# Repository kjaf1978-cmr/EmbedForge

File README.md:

# EmbedForge

An offline-first desktop application that turns a plain-English description and a target
board into a verified, documented Arduino / Raspberry Pi / Pico project: firmware, pin map,
schematic, breadboard, PCB or perfboard, manufacturing files, BOM, emulation and assembly
guide.

Licence: GPL-3.0-or-later (LICENSE file added with the first code, Increment 1).

## Current state
**Increment 1 in progress.** Phase 0 is approved with conditions (docs/phase0/phase0_gate_report.md).
WP 1.1 (Rust core), WP 1.2 (application shell and UI) and WP 1.3 (packaging, signing,
installers, privileged-helper skeleton) are done; reports in docs/inc1/.

- Requirements baseline: `docs/requirements/EmbedForge_prompt_v3.8.md`
- v3 review findings (D9): `docs/requirements/v3_review_findings.md`
- Phase 0 tracker and decisions: `docs/phase0/STATUS.md`
- Session log: `docs/SESSION_LOG.md`

## Layout
```
docs/requirements/   build prompt baselines, review findings, change logs
docs/phase0/         Phase 0 deliverables (a)–(o)
docs/inc1/           Increment 1 scope and reports
core/                Rust workspace: ef-schema, ef-cm, ef-integrity, ef-host, ef-diag,
                     ef-pack (packs, media, bootstrap), ef-helper (SS-05 policy), ef-release
app/ui/              UI (Preact + TypeScript + Vite), unit and browser tests
app/src-tauri/       Tauri 2 desktop shell
packaging/           staging tree, .deb and Windows (NSIS) installers, test media
docs/release/        signing and key-rotation procedure (SEC-02)
spikes/              Phase 0 evaluation code (not application code)
.github/workflows/   CI
tools/               scripts used to produce or check documents
```

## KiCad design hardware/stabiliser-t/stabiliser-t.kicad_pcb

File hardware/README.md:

# Boards of the worked designs (decisions D43, D44)

Each design's board as a KiCad 7 project, with its fabrication files. The boards are generated
from the app's schematics by `tools/kicad` and then checked with KiCad's design rule check
(DRC); do not edit the board files by hand without updating the plan in
`tools/kicad/layouts.ts`, or the next export overwrites the change.

| Design | Folder | Board | DRC (errors / unconnected) | Status |
|---|---|---|---|---|
| Mains voltage stabiliser 1 kVA (P4) | `stabiliser/` | 230 × 246 mm, 2 layers, 2 oz | 0 / 0 | re-routed after the review (input relay, protection relay, IRM-15 supply); the DRC report's warnings: footprint library not registered for the check (193), silkscreen overlaps (78), 4 coil stubs the router bypassed (a dangling end, no open connection); the relay footprint is provisional until checked against the 832A drawing |
| Mains change-over 1P, 32 A (P3): control board + DIN-rail panel | `changeover-1p/` | 165 × 110 mm, 2 layers, 2 oz | 0 / 0 | routed (revision B, D64: the varistors' room for the TMOV14's datasheet body); panel wiring in `panel.csv` |
| Mains change-over 3P+N, 32 A (P3): control board + DIN-rail panel | `changeover-3p/` | 235 × 155 mm, 2 layers, 2 oz | 0 / 0 | routed (revision B, D64: the varistors' room for the TMOV14's datasheet body); panel wiring in `panel.csv` |
| MPPT solar charger 48 V, 80 A (P6): power board | `mppt-power/` | 280 × 160 mm, 2 layers, 4 oz | 0 / 0 | routed; copper bars and lugs below |
| MPPT solar charger 48 V, 80 A (P6): control board | `mppt-control/` | 160 × 110 mm, 2 layers, 2 oz | 0 / 0 | routed; `link.csv`: the nets to the power board |
| Inverter 48 V 5 kW, 50 Hz transformer (P7a): power board | `inverter-lf-48-power/` | 280 × 170 mm, 2 layers, 4 oz | 0 / 0 | routed; copper bars and lugs, bus and ground planes |
| Inverter 48 V 5 kW, 50 Hz transformer (P7a): control board | `inverter-lf-48-control/` | 200 × 150 mm, 2 layers, 2 oz | 0 / 0 | routed; mains nets 3.2 mm apart |
| Inverter 48 V 5 kW, high-frequency (P7b): battery-side power board | `inverter-hf-48-power-lv/` | 180 × 230 mm, 2 layers, 4 oz | 0 / 0 | routed; copper bars, the current transformer off-board |
| Inverter 48 V 5 kW, high-frequency (P7b): 380 V power board | `inverter-hf-48-power-hv/` | 140 × 270 mm, 2 layers, 4 oz | 0 / 0 | routed; conformal coating required (0.8 mm, IPC-2221 B4); the drivers' HVG poured after routing |
| Inverter 48 V 5 kW, high-frequency (P7b): battery-side control board | `inverter-hf-48-control-lv/` | 220 × 160 mm, 2 layers, 2 oz | 0 / 0 | routed; `panel.csv`: the nets to the other boards (J_PANEL, J_PANEL2) |
| Inverter 48 V 5 kW, high-frequency (P7b): 380 V control board | `inverter-hf-48-control-hv/` | 340 × 240 mm, 2 layers, 2 oz | 0 / 0 | routed; 380 V nets 2.5 mm from the battery side; HVG poured on both layers; 77 links drawn by `tools/kicad/autolink.py`; `panel.csv`: the nets to the other boards |
| Inverter 12 V 1.5 kW, 50 Hz transformer (P7a): power board | `inverter-lf-12-power/` | 280 × 170 mm, 2 layers, 4 oz | 0 / 0 | routed; the 48 V board's plan with six 4700 µF bus capacitors |
| Inverter 12 V 1.5 kW, 50 Hz transformer (P7a): control board | `inverter-lf-12-control/` | 200 × 150 mm, 2 layers, 2 oz | 0 / 0 | routed; mains nets 3.2 mm apart; one link drawn by `tools/kicad/link.py` |
| Inverter 12 V 1.5 kW, high-frequency (P7b): battery-side power board | `inverter-hf-12-power-lv/` | 260 × 230 mm, 2 layers, 4 oz | 0 / 0 | routed; three MOSFETs per switch (twelve in the row), copper bars |
| Inverter 12 V 1.5 kW, high-frequency (P7b): 380 V power board | `inverter-hf-12-power-hv/` | 140 × 270 mm, 2 layers, 4 oz | 0 / 0 | routed; the 48 V board's plan; conformal coating required |
| Inverter 12 V 1.5 kW, high-frequency (P7b): battery-side control board | `inverter-hf-12-control-lv/` | 220 × 160 mm, 2 layers, 2 oz | 0 / 0 | routed; `panel.csv`: the nets to the other boards |
| Inverter 12 V 1.5 kW, high-frequency (P7b): 380 V control board | `inverter-hf-12-control-hv/` | 340 × 240 mm, 2 layers, 2 oz | 0 / 0 | routed; as the 48 V one (HVG pours, links by `autolink.py`) |
| Gate controller 24 V (P9, D25): motor drive, protections, Arduino Nano and IR receiver | `gate-controller/` | 160 × 110 mm, 2 layers, 2 oz | 0 / 0 | routed (revision D, after the independent review: a power-on reset, CLR by its edge, a trip drops the relays, a 0.1 s blanking, STOP, the photo-beam transmitter switched for its test, a key-switch input, a CUT-OFF LED; revision C: the close limit and the photo-beam on separate inputs, a LEARN button, the relays on the 832A footprint) |
| Pump controller (P9): tank level, dry source, timers | `pump-control/` | 165 × 110 mm, 2 layers, 2 oz | 0 / 0 | routed (revision C, P9 audit and review): the control is SELV (not earthed), the only mains on the board the safety transformer's fused primary, 5.5 mm from the control; the relays (reinforced interface relays), contactor and breaker on the DIN rail per `panel.csv` |
| Cordless trimmer drive 36 V (P9) | `trimmer-drive/` | 160 × 100 mm, 2 layers, 4 oz | 0 / 0 | routed; power on 3 mm tracks, ground poured on both layers |
| Block moulding machine (P9): safety circuit, high-side outputs, inputs and Arduino Mega 2560 + DIN-rail panel | `block-machine/` | 260 × 180 mm, 2 layers, 2 oz | 0 / 0 | routed (revision C after the second review: the 24 V supplies on their own block, the enable MOSFET on TO-220, F3, K5 for the feeder and vibrators; revision B, D65 … D67: the safety relays, the safety and motor contactors, the breakers on the DIN rail; the outputs switched on their +24 V side with the common enable and read-back; the Mega 2560 under the board, its jacks at the right edge); wiring in `panel.csv`; no 400 V net on the board |
| Irrigation controller (P9, D24): main board | `irrigation-main/` | 130 × 100 mm, 2 layers, 2 oz | 0 / 0 | routed; ESP32-DevKitC on sockets (antenna over the top edge), 24 V in, bus to the modules (20-way ribbon) |
| Irrigation controller (P9, D24): 8-zone channel module (1 … 8 per controller) | `irrigation-module/` | 230 × 95 mm, 2 layers, 2 oz | 0 / 0 | routed; field terminals along the bottom edge (per zone: valve +24 V, valve out, sensor +3.3 V, signal, 0 V); bus in top left, out top right |
| Grinder drive 2.5 kW, 240 V (P9, D26/D46): power board | `grinder-240-power/` | 160 × 110 mm, 2 layers, 4 oz | 0 / 0 | routed; GBPC3510 bridge and both IKW50N60T on the bottom edge (one heatsink, insulating pads), 3 mm power tracks, ground poured on both layers; the whole board at mains potential: 0.8 mm between nets (1.5 mm around the mains input), conformal coating required; the 15 mH choke, the motor and the contactor KM on the panel (`panel.csv`) |
| Grinder drive 2.5 kW, 240 V (P9, D26/D46): control board | `grinder-240-control/` | 180 × 130 mm, 2 layers, 2 oz | 0 / 0 | routed (the run chain and the speed pot moved to the operator interface board); the five trimmers (MAX, MIN, ACCEL, CURRENT LIMIT, IR COMP), terminals for E-STOP, STOP, START, the thermal switch, the reversing switch's contact and the speed pot; not isolated from the mains (DFMEA GR-9): inside the closed enclosure only; one link drawn by `tools/kicad/link.py` |
| Grinder drive 2.5 kW, 240 V (P9, D26/D46): operator interface board | `grinder-240-interface/` | 120 × 90 mm, 2 layers, 2 oz | 0 / 0 | routed; the PELV side (run chain, E-STOP, STOP, START, thermal and reversing contacts, QEN for the K1 and KM coils, the speed pot with MAX and MIN, its TL431 reference) and the barrier: the AMC1311B (set point) and the PC817 (fault); 5.5 mm between the PELV nets and the control's side (GND, V12, VD2, SPP, SPN, OKA: J_MAINS, its spare pole on V12); TR1 on the panel |
| Grinder drive 2.5 kW, 24 V battery (P9, D26/D46): power board | `grinder-24-power/` | 200 × 130 mm, 2 layers, 4 oz | 0 / 0 | routed; six IRFP4468 on the bottom edge, the switch node a 6 mm bar between the row and the edge (tin it), bus plane over 8 × 2200 µF, ground plane, the motor's return poured to the 0.5 mΩ shunt; M5 lugs for battery +/−, motor A+/A−; the 200 A fuse, KM (250 A) and K1 on the panel |
| Grinder drive 2.5 kW, 24 V battery (P9, D26/D46): control board | `grinder-24-control/` | 180 × 130 mm, 2 layers, 2 oz | 0 / 0 | routed; the 240 V control's circuit with the 24 V scaling and the battery's 21 V cut-off |
| Mains stabiliser 5/10/15 kVA, contactor taps (P4b, D58): control board | `stabiliser-t/` | 270 × 185 mm, 2 layers, 2 oz | 0 / 0 | routed; mains nets 3.2 mm apart; the contactors, breakers, 24 V supply and autotransformer on the DIN rail, wired per `panel.csv` (power poles never through the board) |

### The 24 V inverters (P7, 3 kW)

The 24 V units use the 48 V boards: the same parts on each board with the same footprints and
connections, only values differ (`tools/kicad/variant.ts` checks this). The 48 V board's folder
holds the 24 V parts list as `<board>-bom-24v.csv`; order the board's fabrication files as they
are and fit the parts from that list.

## What a folder holds

- `<design>.kicad_pcb`, `.kicad_pro`, `.kicad_dru`: the board, its net classes and the custom
  insulation rule. Open the `.kicad_pro` in KiCad 7 or later.
- `<design>-fabrication.zip`: Gerber (copper, solder mask, silkscreen, outline), Excellon drill
  file and drill map, pick-and-place positions. Upload it to the fab as it is.
- `<design>-copper.pdf` / `.png`: both copper layers, the silkscreen and the outline.
- `<design>-drc.rpt`: KiCad's DRC report of the routed board.
- `panel.csv`: for designs with parts on a panel (DIN rail, chassis), the wiring list.
- `fp-lib-table` with `../NETApps.pretty`: the app's footprints as a KiCad library.

## Rules every board follows

- Mains nets (found from the schematic: everything galvanically joined to L and N, up to the
  transformers, optocouplers and relay coils) are 3.2 mm from every other net, the creepage of
  basic insulation at 300 V r.m.s. (IEC 62368-1, pollution degree 2, material group IIIb); the
  control side is earthed (PE), so basic insulation suffices. Between two mains nets 1.5 mm.
- Mains terminals at 7.62 mm pitch; off-board transformers on connectors with an empty pole
  between their windings.
- Footprints follow each part's value and rating, as the parts list orders it: electrolytics by
  C·V (Ø 5 … 18 mm radial, 22 … 35 mm snap-in), film capacitors by C·V (7.5 … 37.5 mm pitch),
  Y and high-voltage ceramics at 10 mm, resistors by power (¼ W, 1 W, 2–3 W, 5 W and 10 W
  cement, four-terminal shunts), fuses (TR5 to 6.3 A, 5 × 20 mm holder to 10 A), inductors (radial
  to 2 A, toroid to 10 A). Parts above that (power resistors over 10 W, inductors over 10 A, fuses
  over 10 A) sit off the board, on the chassis or heatsink, wired or bolted.
- High-current nets end on M5 bolt lugs (busbars or cable lugs), not on screw terminals.
- Track widths by IPC-2221 for the current at 20 K rise in 2 oz copper (the stabiliser's mains
  tracks 1.6 mm for 7 A).
- The power section is placed and partly routed by a written plan (`tools/kicad/layouts.ts`);
  the control section is placed from the schematic and routed by Freerouting.

## Power boards (D45)

The high-current paths are drawn as 4 mm tracks with the solder mask open on them: solder a
tinned copper bar 4 × 3 mm (12 mm², 80 A at about 30 K rise) along each, or two 4 mm² solid
copper wires, so the bar carries the current and the board's 4 oz copper only joins it to the
pins. Cables and busbars bolt to the M5 lugs (plated holes with 12 mm rings): the inductor and
the fuse sit on the chassis next to the board. The TO-247 and TO-126 parts stand in one row along
the bottom edge, their tabs to a common heatsink (isolate each tab with a thermal pad rated for
the voltage, the PV side reaches 114 V). The two boards of a design connect through their 12-pole
connectors, pole by pole as `link.csv` lists them.

## Parts lists

Each folder's `<design>-bom.csv` lists the parts with the footprint each has on the board, the
manufacturer's part number, distributors with order numbers, and an indicative unit price (EUR,
October 2026, "live" or "estimate"; check prices and stock when ordering). The lines not on
this board come last (panel parts, the other board's parts).

## Known warnings

- `lib_footprint_mismatch` on parts turned 180°: KiCad compares the turned reference text's angle
  with the library copy; the copper is the same.
- `silk_overlap`: reference designators touching outlines (cosmetic; fix by hand before ordering
  if the silkscreen matters).

## Before ordering

These boards come out of the verified schematics, but no one has built them yet. Before a
production order: a person's review of the layout (clearances on the mains side, the heat of the
relays and regulators), and a prototype tested against the design's test plan (TEST_REPORT.md).
Prices and parts: the design document's BOM (`docs` export in the app).

Regenerate a board:

```
cd app/ui && npx vite-node ../../tools/kicad/export.ts stabiliser /tmp/stab
cd ../.. && python3 tools/kicad/route.py /tmp/stab --passes 40
```

Check every board against its schematic as the app builds it now (the same parts, every pad on
the same net, the parts list current; `--fix-bom` rewrites stale parts lists):

```
cd app/ui && npx vite-node ../../tools/kicad/check.ts
```

Needs KiCad 7 (pcbnew Python module and kicad-cli), Freerouting 1.9 at
/opt/freerouting/freerouting.jar (or `FREEROUTING=`), Java 17+ and xvfb-run.

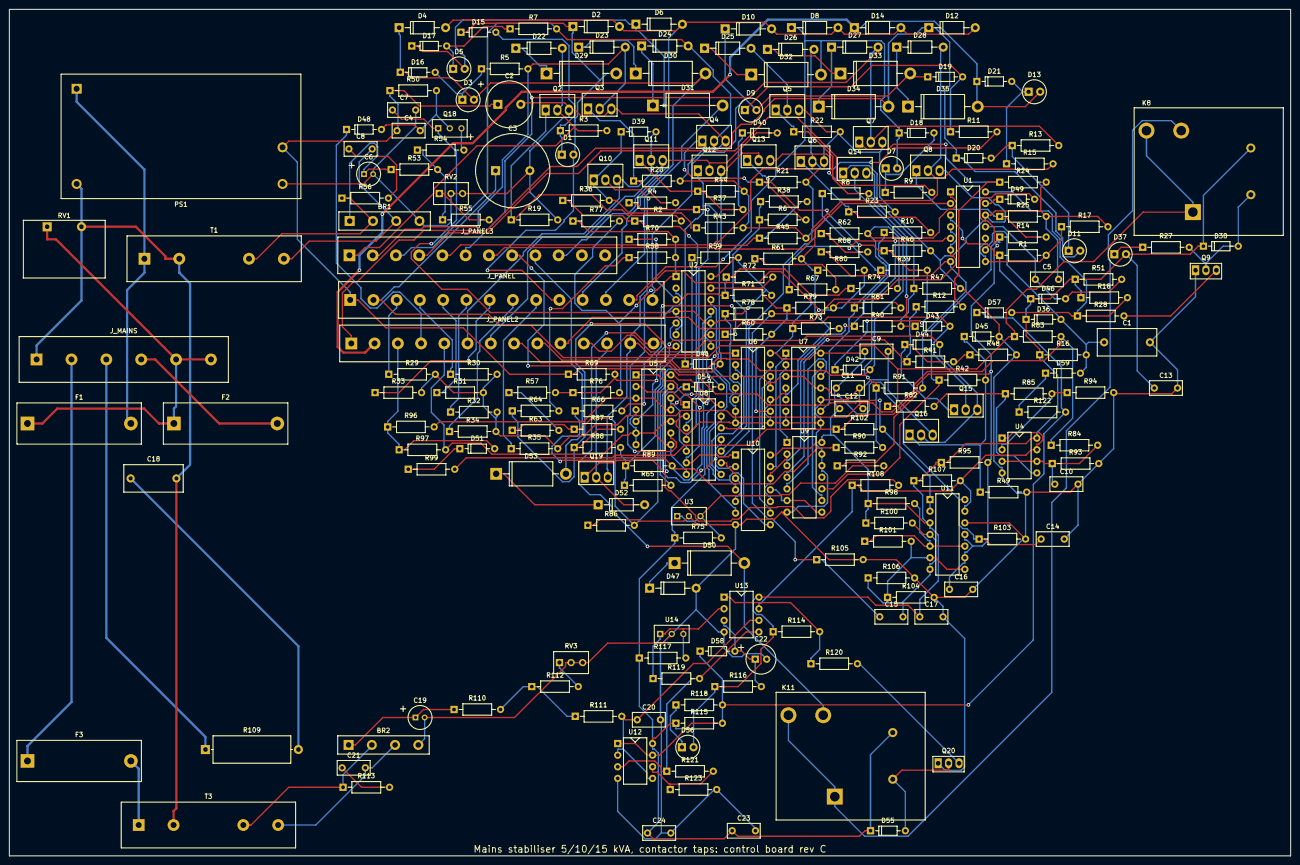
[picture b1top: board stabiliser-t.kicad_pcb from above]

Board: 2 copper layers, 280.0 x 185.0 mm, 253 parts (0 on the bottom side), 166 nets.

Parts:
BR1, BR2: DB107; Bridge_Inline_4
C1: 4.7u; C_Film_P10
C2: 100u; CP_Radial_D10
C3: 470u; CP_Radial_D16
C4, C16: 1u; C_Disc_5.08
C5, C7, C10, C20: 470n; C_Disc_5.08
C6, C19: 4.7u; CP_Radial_D5
C8, C9, C11, C12, C13, C14, C15, C17, C21, C23, C24: 100n; C_Disc_5.08
C18: 220n; C_Film_P10
C22: 22u; CP_Radial_D6.3
D1, D3, D5, D7, D9, D11, D13: yellow; LED_D5.0
D2, D4, D6, D8, D10, D12, D14, D22, D23, D24, D25, D26, D27, D28, D47, D52: 1N4007; D_DO-41
D15, D16, D17, D18, D19, D20, D21, D36, D38, D46, D48, D49, D51, D55, D57, D58, D59: 1N4148; D_DO-35
D29, D30, D31, D32, D33, D34, D35, D50, D53: 1.5KE27A; D_DO-201AD
D37: green; LED_D5.0
D39, D40, D41, D42, D43, D44, D45, D54: BZX55C13; D_DO-35
D56: red; LED_D5.0
F1: 1; Fuseholder_5x20
F2: 2; Fuseholder_5x20
F3: 0.5; Fuseholder_5x20
J_MAINS: mains to the panel; TerminalBlock_1x6_P7.62
J_PANEL, J_PANEL2: to the panel; TerminalBlock_1x14
J_PANEL3: to the panel; TerminalBlock_1x12
K8, K11: 12 V 30 A; Relay_SPDT_832A
PS1: IRM-15-12; IRM-15
Q2, Q3, Q4, Q5, Q6, Q7, Q8, Q10, Q11, Q12, Q13, Q14, Q15, Q16, Q19: IRF540N; TO-220_Vertical
Q9, Q20: BD139; TO-126_Vertical
Q18: 2N7000; TO-92_Wide
R1: 2.49k; R_Axial_0207
R2, R4, R6, R8, R10, R12, R14, R102: 1k; R_Axial_0207
R3, R5, R7, R9, R11, R13, R15, R118: 4.7k; R_Axial_0207
R16, R51, R57, R58, R59, R60, R61, R62, R63, R64, R65, R66, R67, R68: 1M; R_Axial_0207
R17, R36, R37, R38, R39, R40, R41, R42, R96, R101, R108, R115, R123: 10k; R_Axial_0207
R18, R27, R28, R29, R30, R31, R32, R33, R34, R35, R69, R70, R71, R72, R73, R74, R75, R83, R97, R107, R114, R117, R120, R122: 2.2k; R_Axial_0207
R19, R20, R21, R22, R23, R24, R25, R43, R44, R45, R46, R47, R48, R49, R54, R76, R77, R78, R79, R80, R81, R84, R98, R100, R103, R104, R105, R106, R111: 100k; R_Axial_0207
R50: 4.7M; R_Axial_0207
R53: 80.6k; R_Axial_0207
R55: 6.8k; R_Axial_0207
R56, R113: 220; R_Axial_0207
R82: 26.1k; R_Axial_0207
R85: 1.74k; R_Axial_0207
R86: 5.36k; R_Axial_0207
R87, R88, R89, R90: 732; R_Axial_0207
R91: 909; R_Axial_0207
R92: 787; R_Axial_0207
R93, R116: 47k; R_Axial_0207
R94: 4.22k; R_Axial_0207
R95: 10M; R_Axial_0207
R99: 61.9k; R_Axial_0207
R109: 100; R_Axial_P20
R110: 806k; R_Axial_0207
R112: 68k; R_Axial_0207
R119: 1.82k; R_Axial_0207
R121: 3.65k; R_Axial_0207
RV1: TMOV14RP300E; TMOV_14
RV2: 5k; Pot_Trimmer_3
RV3: 50k; Pot_Trimmer_3
T1, T3: 0.06; Transformer_Wires_P7.62
U1, U2, U11: LM339; DIP-14
U3, U14: TL431; TO-92_Wide
U4, U12, U13: LM393; DIP-8
U5, U6, U7, U8, U9, U10: +12V; DIP-14

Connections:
+12V: C2.1, C4.1, C9.1, C11.1, C12.1, C13.1, C17.1, C23.1, C24.1, D36.1, D37.2, D38.1, D46.1, D55.1, D56.2, J_PANEL.1, K8.1, K11.1, PS1.+V, R1.1, R16.1, R18.1, R50.1, R51.1, R69.1, R70.1, R71.1, R72.1, R73.1, R74.1, R75.1, R95.1, R98.1, R100.1, R107.1, R114.1, R115.1, R116.1, R117.1, U1.3, U2.3, U4.8, U5.14, U6.14, U7.14, U8.14, U9.14, U10.14, U11.3, U12.8, U13.8
+24V: C3.1, J_PANEL.2, K8.3, K8.4, R82.1, R83.1
AX1: J_PANEL.3, R29.1
AX2: J_PANEL.4, R30.1
AX3: J_PANEL.5, R31.1
AX4: J_PANEL.6, R32.1
AX5: J_PANEL.7, R33.1
AX6: J_PANEL.8, R34.1
AX7: J_PANEL.9, R35.1
B3: U8.9, U10.3, U10.5
B4: U8.13, U10.4, U10.8
B5: U9.2, U10.10, U10.12
B6: U9.6, U9.8, U10.11
BD: Q9.3, R28.2
BP: Q20.3, R120.2
BPP: C22.1, D58.2, R116.2, U13.3
CF1: D1.2, D2.1, D15.1, D29.2, J_PANEL.10
CF2: D3.2, D4.1, D16.1, D30.2, J_PANEL.11
CF3: D5.2, D6.1, D17.1, D31.2, J_PANEL.12
CF4: D7.2, D8.1, D18.1, D32.2, J_PANEL.13
CF5: D9.2, D10.1, D19.1, D33.2, J_PANEL.14
CF6: D11.2, D12.1, D20.1, D34.2, J_PANEL2.1
CF7: D13.2, D14.1, D21.1, D35.2, J_PANEL2.2
CLK: C14.1, R96.2, R103.1, U5.3, U5.11, U6.3, U6.11, U7.3, U7.11, U11.14
CLKP: D51.2, J_PANEL2.3, R96.1, R97.1
DF2K: D59.1, R122.1
DIZ: D52.1, D53.1
DKZ: D47.1, D50.1
DLY: C1.1, D36.2, D59.2, R16.2, U1.9
DSHK: D48.1, J_PANEL2.4
DTH: R1.2, R17.1, U1.8, U1.10
DZT1: D22.1, D29.1
DZT2: D23.1, D30.1
DZT3: D24.1, D31.1
DZT4: D25.1, D32.1
DZT5: D26.1, D33.1
DZT6: D27.1, D34.1
DZT7: D28.1, D35.1
E: C15.2, R100.2, R106.1, U11.4, U11.7
FLTS: D57.1, D58.1, R115.2, R118.2, R122.2, U12.1, U12.7
GB1: D39.1, Q10.1, R36.2, R43.1
GB2: D40.1, Q11.1, R37.2, R44.1
GB3: D41.1, Q12.1, R38.2, R45.1
GB4: D42.1, Q13.1, R39.2, R46.1
GB5: D43.1, Q14.1, R40.2, R47.1
GB6: D44.1, Q15.1, R41.2, R48.1
GB7: D45.1, Q16.1, R42.2, R49.1
GI: D54.1, Q19.1, R108.2
GND: BR1.4, BR2.4, C1.2, C2.2, C3.2, C5.2, C6.2, C7.2, C9.2, C10.2, C11.2, C12.2, C13.2, C14.2, C16.2, C17.2, C19.2, C20.2, C22.2, C23.2, C24.2, D45.2, D47.2, J_PANEL2.5, PS1.-V, Q2.3, Q3.3, Q4.3, Q5.3, Q6.3, Q7.3, Q8.3, Q9.1, Q16.3, Q20.1, R17.2, R19.2, R20.2, R21.2, R22.2, R23.2, R24.2, R25.2, R43.2, R44.2, R45.2, R46.2, R47.2, R48.2, R49.2, R86.1, R93.2, R94.2, R97.2, R103.2, R104.2, R105.2, R106.2, R123.2, RV2.2, RV2.3, RV3.2, RV3.3, U1.12, U2.12, U3.2, U4.4, U5.4, U5.6, U5.7, U5.8, U5.10, U6.4, U6.6, U6.7, U6.8, U6.10, U7.4, U7.6, U7.7, U7.8, U7.10, U8.2, U8.7, U9.7, U9.12, U9.13, U10.7, U11.12, U12.4, U13.4, U14.2
GSH: C4.2, D48.2, Q18.2, R50.2
GT1: Q2.1, R2.2, R19.1
GT2: Q3.1, R4.2, R20.1
GT3: Q4.1, R6.2, R21.1
GT4: Q5.1, R8.2, R22.1
GT5: Q6.1, R10.2, R23.1
GT6: Q7.1, R12.2, R24.1
GT7: Q8.1, R14.2, R25.1
KC1: D39.2, J_PANEL2.6, Q10.3, Q11.2
KC2: D40.2, J_PANEL2.7, Q11.3, Q12.2
KC3: D41.2, J_PANEL2.8, Q12.3, Q13.2
KC4: D42.2, J_PANEL2.9, Q13.3, Q14.2
KC5: D43.2, J_PANEL2.10, Q14.3, Q15.2
KC6: D44.2, J_PANEL2.11, Q15.3, Q16.2
KD: D38.2, K8.2, Q9.2, R27.2
KIC: D52.2, J_PANEL2.12, Q19.2
KIS: D54.2, J_PANEL2.13, Q10.2, Q19.3
KMC: D50.2, J_PANEL2.14, K11.5
KMC1: K8.5, K11.3, K11.4
KPC: D55.2, K11.2, Q20.2
KT1: D22.2, J_PANEL3.1, Q2.2, R3.2
KT2: D23.2, J_PANEL3.2, Q3.2, R5.2
KT3: D24.2, J_PANEL3.3, Q4.2, R7.2
KT4: D25.2, J_PANEL3.4, Q5.2, R9.2
KT5: D26.2, J_PANEL3.5, Q6.2, R11.2
KT6: D27.2, J_PANEL3.6, Q7.2, R13.2
KT7: D28.2, J_PANEL3.7, Q8.2, R15.2
LFA: D56.1, R118.1
LKOA: D37.1, R27.1
LN1: U5.2, U8.1
LN2: U5.12, U8.5
LN3: U6.2, U8.8
LN4: U6.12, U8.12
LN5: U7.2, U9.1
LN6: U7.12, U9.5
LO1: U5.1, U8.6, U10.1
LO2: U5.13, U10.2
LO3: U6.1, U10.6
LO4: U6.13, U10.9
LO5: U7.1, U10.13
LO6: U7.13, U9.9
LTA1: D1.1, D15.2, R3.1
LTA2: D3.1, D16.2, R5.1
LTA3: D5.1, D17.2, R7.1
LTA4: D7.1, D18.2, R9.1
LTA5: D9.1, D19.2, R11.1
LTA6: D11.1, D20.2, R13.1
LTA7: D13.1, D21.2, R15.1
M: R29.2, R30.2, R31.2, R32.2, R33.2, R34.2, R35.2, R83.2, R84.1
MS: C10.1, R84.2, R93.1, U4.3, U4.6
MT: C16.1, D49.2, R95.2, R99.2, R102.1, U11.9, U11.11
MTP: D51.1, R99.1
N: C18.2, J_MAINS.1, PS1.N, RV1.2, T1.2, T3.2
N1: R63.1, R86.2, R87.1, U2.5
N2: R64.1, R87.2, R88.1, U2.7
N3: R65.1, R88.2, R89.1, U2.9
N4: R66.1, R89.2, R90.1, U2.11
N5: R67.1, R90.2, R91.1, U1.5
N6: R68.1, R91.2, R92.1, U1.7
NF1: R57.1, R63.2
NF2: R58.1, R64.2
NF3: R59.1, R65.2
NF4: R60.1, R66.2
NF5: R61.1, R67.2
NF6: R62.1, R68.2
O1: R57.2, R69.2, R76.1, U2.2, U5.5
O2: R58.2, R70.2, R77.1, U2.1, U5.9
O3: R59.2, R71.2, R78.1, U2.14, U6.5
O4: R60.2, R72.2, R79.1, U2.13, U6.9
O5: R61.2, R73.2, R80.1, U1.2, U7.5
O6: R62.2, R74.2, R81.1, U1.1, U7.9
OD: D57.2, R18.2, R28.1, U1.14
OI: R107.2, R108.1, U4.1, U4.7, U11.13, U13.7
OKP: R114.2, R120.1, U13.1
PGC: C5.1, D46.2, R51.2, U1.11
PGN: D49.1, U1.13
S1: R2.1, R36.1, U8.3
S2: R4.1, R37.1, U8.4
S3: R6.1, R38.1, U8.10
S4: R8.1, R39.1, U8.11
S5: R10.1, R40.1, U9.3
S6: R12.1, R41.1, U9.4
S7: R14.1, R42.1, U9.10
SA: BR1.2, R56.1, T1.3
SA2: BR2.2, R113.1, T3.3
SB: BR1.3, C8.2, T1.4
SB2: BR2.3, C21.2, T3.4
SEN2: R110.2, R111.1, R112.1
SENSE: R53.2, R54.1, R55.1
SF: C7.1, Q18.1, U1.4, U1.6, U2.4, U2.6, U2.8, U2.10
SF2: C20.1, R111.2, U12.2, U12.5, U13.6
SFI: Q18.3, R54.2
SN: C8.1, R56.2
SN2: C21.1, R113.2
SNKI: C18.1, R109.2
STR: R55.2, RV2.1
STR2: R112.2, RV3.1
SUM: C15.1, R76.2, R77.2, R78.2, R79.2, R80.2, R81.2, R105.1
T5: F3.1, J_MAINS.2
T5F: F3.2, T3.1
TRG: J_PANEL3.8, R102.2, U11.1, U11.2
V24C: D53.2, J_PANEL3.9
VCH: J_MAINS.3, R109.1
VEH: R98.2, R101.1, U11.5, U11.10
VEL: R101.2, R104.1, U11.6, U11.8
VF: F1.2, PS1.L, T1.1
VF2: F2.2, J_MAINS.4
VIN: F1.1, F2.1, J_MAINS.5, J_MAINS.6, RV1.1
VOV: R119.2, R121.1, U12.3, U13.5
VREF: R75.2, R92.2, U3.1, U3.3
VREF2: R117.2, R119.1, U13.2, U14.1, U14.3
VSR: BR1.1, C6.1, R53.1
VSR2: BR2.1, C19.1, R110.1
VTF: D2.2, D4.2, D6.2, D8.2, D10.2, D12.2, D14.2, J_PANEL3.10
VUV: R121.2, R123.1, U12.6
VWH: R82.2, R85.1, U4.5
VWL: R85.2, R94.1, U4.2

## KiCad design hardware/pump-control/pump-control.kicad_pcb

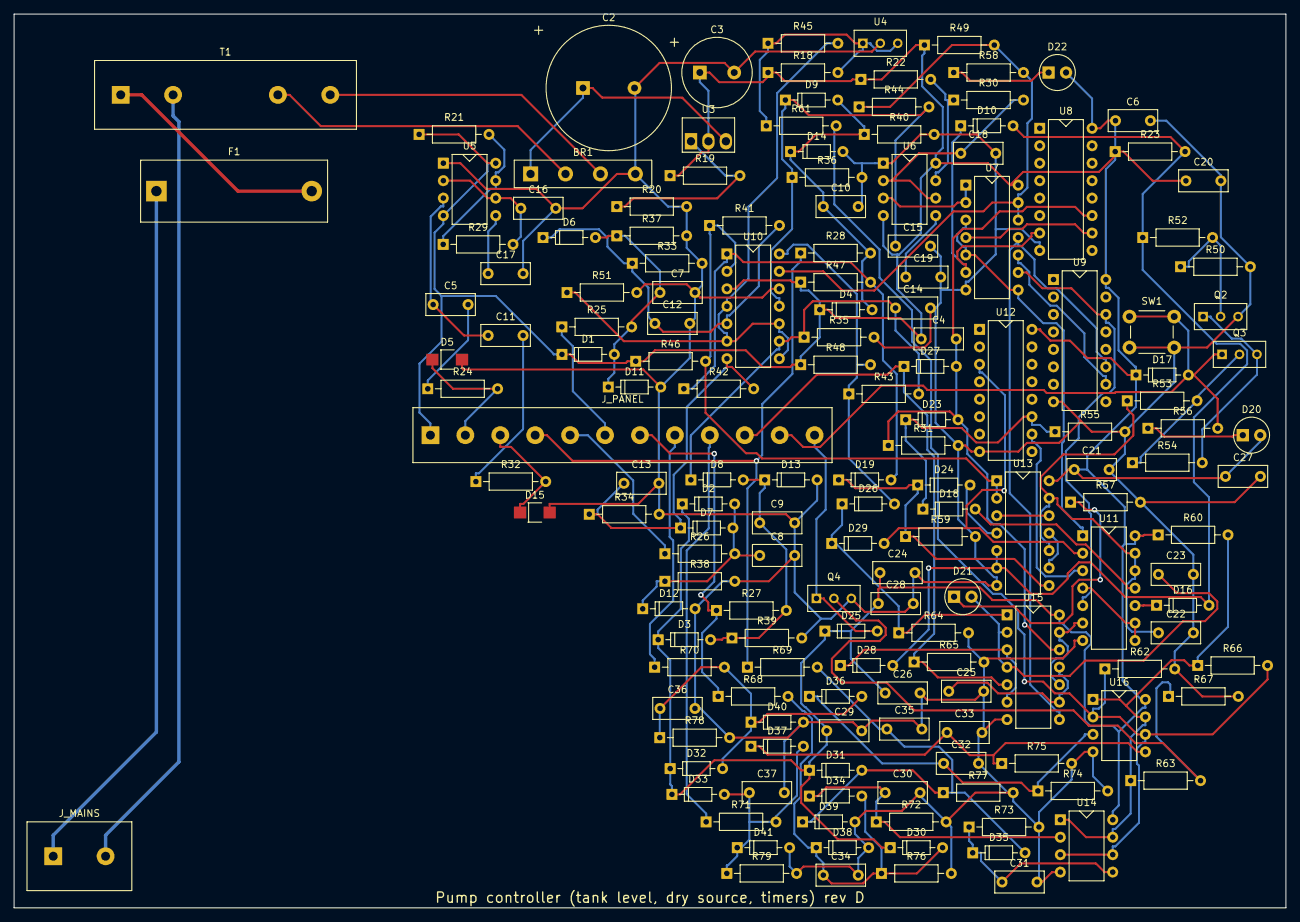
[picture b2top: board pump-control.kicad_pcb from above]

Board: 2 copper layers, 185.0 x 130.0 mm, 162 parts (0 on the bottom side), 85 nets.

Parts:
BR1: DB107; Bridge_Inline_4
C2: 1000u; CP_Radial_D18
C3: 100u; CP_Radial_D10
C4, C5, C11, C12, C13, C14, C15, C18, C30, C31, C32, C33: 1u; C_Disc_5.08
C6, C7, C8, C9, C10, C16, C20, C21, C24, C26, C27, C28, C29, C34, C35, C36, C37: 100n; C_Disc_5.08
C17, C19, C22, C23, C25: 10n; C_Disc_5.08
D1, D2, D3, D4, D6, D7, D8, D9, D10, D11, D12, D13, D14, D16, D17, D18, D19, D23, D24, D25, D26, D27, D28, D29, D30, D31, D32, D33, D34, D35, D36, D37, D38, D39, D40, D41: 1N4148; D_DO-35
D5, D15: SMAJ12CA; D_SMA
D20: green; LED_D5.0
D21: red; LED_D5.0
D22: yellow; LED_D5.0
F1: 0.2; Fuseholder_5x20
J_MAINS: mains to the panel; TerminalBlock_1x2_P7.62
J_PANEL: to the panel; TerminalBlock_1x12
Q2, Q3, Q4: BC547B; TO-92_Wide
R18, R56, R58: 2.2k; R_Axial_0207
R19: 240; R_Axial_0207
R20: 2.05k; R_Axial_0207
R21, R22, R23, R25, R26, R27, R28, R45, R46, R47, R48, R49, R60, R61, R68, R69, R70, R71: 10k; R_Axial_0207
R24, R32: 1k; R_Axial_0207
R29: 68k; R_Axial_0207
R30: 680k; R_Axial_0207
R31, R55, R59, R64, R65: 100k; R_Axial_0207
R33, R34, R35, R36, R72, R73, R74, R75: 220k; R_Axial_0207
R37, R38, R39, R40, R53, R63, R76, R77, R78, R79: 22k; R_Axial_0207
R41, R42, R43, R44, R66: 10M; R_Axial_0207
R50, R52, R54, R67: 47k; R_Axial_0207
R51, R62: 9.09k; R_Axial_0207
R57: 4.7k; R_Axial_0207
SW1: false; SW_Tactile_6mm
T1: 0.075; Transformer_Wires_P7.62
U3: LM317HV; TO-220_Vertical
U4: TL431; TO-92_Wide
U5, U6: NE555; DIP-8
U7, U11, U13, U15: +12V; DIP-14
U8, U9, U12: +12V; DIP-16
U10: LM339; DIP-14
U14, U16: LM393; DIP-8

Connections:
+12V: C3.1, C4.1, C6.1, C20.1, C21.1, C24.1, C26.1, C27.1, C28.1, C29.1, D1.1, D2.1, D3.1, D4.1, D17.1, D20.2, D22.2, D25.1, D30.1, D31.1, D32.1, D33.1, J_PANEL.1, R18.1, R19.1, R21.1, R22.1, R23.1, R46.1, R47.1, R48.1, R49.1, R60.1, U3.2, U5.4, U5.8, U6.4, U6.8, U7.14, U8.16, U9.16, U10.3, U11.14, U12.16, U13.14, U14.8, U15.14, U16.8
ADJ: R19.2, R20.1, U3.1
BQ: Q3.2, R53.2, R54.1
BQ2: Q4.2, R63.2, R67.1
BQP: Q2.2, R50.1, R52.2
CK1: U7.4, U8.10
CK2: U7.10, U9.10
CK3: U11.3, U12.10
CLK: U6.3, U7.1, U7.2
CLKN: U7.3, U7.5, U7.8, U11.1
DOK: U7.9, U9.14, U11.5
DOKE: D16.1, U11.10
DOKN: U11.4, U11.8, U11.9
DSN: U11.6, U15.10, U15.13
DSQ: C25.1, U15.9, U15.11
EC1: D5.1, J_PANEL.2, R24.2
EC2: D15.1, J_PANEL.3, R32.2
ED: J_PANEL.4, R28.1, R69.1
EH: J_PANEL.5, R26.1
EL: J_PANEL.6, R25.1
EO: J_PANEL.7, R27.1, R68.1
ER1: J_PANEL.8, R70.1
ER2: J_PANEL.9, R71.1
EX1: C5.2, R24.1
EX2: C11.2, R32.1
EXO: C5.1, C11.1, U5.3
FLTN: D28.1, U15.3, U15.6
FLTQ: C23.1, D21.2, U15.2, U15.4
FRES: D27.1, J_PANEL.10, R65.1, U15.5
FSET: D26.1, D29.1, R64.1, U15.1
GND: BR1.4, C2.2, C3.2, C6.2, C7.2, C8.2, C9.2, C10.2, C12.2, C13.2, C14.2, C15.2, C16.2, C17.2, C18.2, C19.2, C20.2, C21.2, C22.2, C23.2, C24.2, C25.2, C26.2, C27.2, C28.2, C29.2, C30.2, C31.2, C32.2, C33.2, C34.2, C35.2, C36.2, C37.2, D5.2, D11.2, D12.2, D13.2, D14.2, D15.2, D38.2, D39.2, D40.2, D41.2, Q2.3, Q4.3, R20.2, R31.2, R33.2, R34.2, R35.2, R36.2, R37.2, R38.2, R39.2, R40.2, R50.2, R51.2, R55.2, R57.2, R59.2, R62.2, R64.2, R65.2, R67.2, R72.2, R73.2, R74.2, R75.2, R76.2, R77.2, R78.2, R79.2, SW1.2a, SW1.2b, U4.2, U5.1, U6.1, U7.7, U8.8, U9.8, U10.12, U11.7, U12.8, U13.7, U14.4, U15.7, U16.4
HD: C15.1, D9.1, R36.1, R44.2, U10.11
HH: C13.1, D7.1, R34.1, R42.2, U10.7
HL: C12.1, D6.1, R33.1, R41.2, U10.5
HO: C14.1, D8.1, R35.1, R43.2, U10.9
JD: C31.1, D35.1, R73.1, U14.5
JO: C30.1, D34.1, R72.1, U14.2
JR1: C32.1, D36.1, R74.1, U16.3
JR2: C33.1, D37.1, R75.1, U16.5
KP: D17.2, J_PANEL.11, Q3.1, R56.2, SW1.1a, SW1.1b
KP2: D25.2, J_PANEL.12, Q4.1
LDA: D22.1, R58.1
LF: F1.2, T1.1
LF2: F1.1, J_MAINS.1
LFA: D21.1, R57.1
LRA: D20.1, R56.1
N: J_MAINS.2, T1.2
NPERM: D24.2, U13.4
NRUN: D18.2, U11.11
NWL: U13.3, U13.12
OK2: R60.2, R63.1, R66.1, U14.1, U14.7, U16.1, U16.7
PD: C10.1, D4.2, D9.2, D14.1, R28.2, R40.1
PERMIT: D10.2, D16.2, D28.2, R23.2, R52.1, U13.5, U13.6
PH: C8.1, D2.2, D7.2, D12.1, R26.2, R38.1
PL: C7.1, D1.2, D6.2, D11.1, R25.2, R37.1
PO: C9.1, D3.2, D8.2, D13.1, R27.2, R39.1
POR: C4.2, D23.2, D27.2, R31.1, U8.11, U15.12
QD: C35.1, D31.2, D35.2, D39.1, R69.2, R77.1
QE: Q2.1, Q3.3, R54.2
QO: C34.1, D30.2, D34.2, D38.1, R68.2, R76.1
QR1: C36.1, D32.2, D36.2, D40.1, R70.2, R78.1
QR2: C37.1, D33.2, D37.2, D41.1, R71.2, R79.1
RDY: D10.1, U7.6, U8.7
RRES: D19.1, D24.1, R59.1, U13.8
RST3: D18.1, D23.1, R55.1, U12.11
RUNN: U13.9, U13.11
RUNQ: C22.1, R53.1, U11.12, U11.13, U13.10, U13.13
SA: BR1.2, T1.3
SB: BR1.3, T1.4
SD: R22.2, R30.1, U6.7
SK: C19.1, U6.5
ST: C18.1, R30.2, U6.2, U6.6
TMAX: D29.2, U11.2, U12.3
VRAW: BR1.1, C2.1, U3.3
VREF: R18.2, R45.1, R61.1, U4.1, U4.3
VT2: R61.2, R62.1, R66.2, U14.3, U14.6, U16.2, U16.6
VTH: R45.2, R51.1, U10.4, U10.6, U10.8, U10.10
WDN: U7.11, U9.11, U15.8
WDO: R44.1, R49.2, R58.2, U7.12, U7.13, U10.13
WHO: D19.2, R42.1, R47.2, U10.1
WLO: R41.1, R46.2, U10.2, U13.1, U13.2
WOO: D26.2, R43.1, R48.2, U10.14
XD: R21.2, R29.1, U5.7
XK: C17.1, U5.5
XT: C16.1, R29.2, U5.2, U5.6

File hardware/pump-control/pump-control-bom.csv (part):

"on this board","qty","references","part","value","details","footprint","MPN","maker","distributors (order numbers)","unit EUR","total EUR","price basis"
"yes","1","BR1","Bridge rectifier","DB107","","Bridge_Inline_4","DB107","various","any distributor (DIP-4)","0.30","0.30","estimate"
"yes","1","C2","Electrolytic capacitor","1 mF","voltage rating 35 V","CP_Radial_D18","1000uF 35 V 105 °C low-ESR long life (series e.g. Nichicon UHW, Panasonic FC/FR)","Nichicon / Panasonic","Future Electronics / Mouser","3.20","3.20","estimate"
"yes","1","C3","Electrolytic capacitor","100 µF","voltage rating 25 V","CP_Radial_D10","100uF 25 V 105 °C (e.g. Panasonic FC series)","Panasonic / Nichicon","any distributor (radial)","0.25","0.25","estimate"
"yes","10","C4 C12 C13 C14 C15 C18 C30 C31 C32 C33","Capacitor","1 µF","voltage rating 50 V","C_Disc_5.08","MKT film 1uF 50 V (e.g. WIMA MKS4, TDK B32529)","WIMA / TDK","any distributor (film)","0.35","3.50","estimate"
"yes","2","C5 C11","Capacitor","1 µF","voltage rating 63 V","C_Disc_5.08","MKT film 1uF 63 V (e.g. WIMA MKS4, TDK B32529)","WIMA / TDK","any distributor (film)","0.35","0.70","estimate"
"yes","17","C6 C7 C8 C9 C10 C16 C20 C21 C24 C26 C27 C28 C29 C34 C35 C36 C37","Capacitor","100 nF","voltage rating 50 V","C_Disc_5.08","ceramic X7R or MKT 100nF 50 V, 5.08 mm","KEMET / Vishay","any distributor (5.08 mm)","0.12","2.04","estimate"
"yes","5","C17 C19 C22 C23 C25","Capacitor","10 nF","voltage rating 50 V","C_Disc_5.08","C0G ceramic 10nF 50 V, 5.08 mm","KEMET / Vishay","any distributor (5.08 mm)","0.10","0.50","estimate"
"yes","36","D1 D2 D3 D4 D6 D7 D8 D9 D10 D11 D12 D13 D14 D16 D17 D18 D19 D23 D24 D25 D26 D27 D28 D29 D30 D31 D32 D33 D34 D35 D36 D37 D38 D39 D40 D41","Diode","1N4148","","D_DO-35","1N4148","various","any distributor (DO-35)","0.06","2.16","estimate"
"yes","2","D5 D15","TVS diode","SMAJ12CA","","D_SMA","SMAJ12CA","Littelfuse","LCSC; Mouser","0.25","0.50","estimate"
"yes","1","D20","LED","green","","LED_D5.0","5 mm green LED, 20 mA","Kingbright (e.g. L-53GD)","any distributor (5 mm LED)","0.12","0.12","estimate"
"yes","1","D21","LED","red","","LED_D5.0","5 mm red LED, 20 mA","Kingbright (e.g. L-53ID)","any distributor (5 mm LED)","0.12","0.12","estimate"
"yes","1","D22","LED","yellow","","LED_D5.0","5 mm yellow LED, 20 mA","Kingbright (e.g. L-53YD)","any distributor (5 mm LED)","0.12","0.12","estimate"
"yes","1","F1","Fuse","T 0.2 A H, 5×20 ceramic","cold resistance 2 Ω","Fuseholder_5x20","5×20 T 0.2 A H ceramic (Schurter SPT 0001.25xx series) + PCB holder 0031.8201","Schurter","Bürklin; Mouser","1.60","1.60","estimate"
"yes","3","Q2 Q3 Q4","NPN transistor","BC547B","","TO-92_Wide","BC547B","onsemi","any distributor (TO-92)","0.10","0.30","estimate"
"yes","3","R18 R56 R58","Resistor","2.2 kΩ","power rating 250 mW","R_Axial_0207","metal film 2.2kΩ 0.6 W, 1 %, 50 ppm/K (e.g. Vishay MBB0207)","Vishay / Yageo","any distributor (0207 1 %)","0.08","0.24","estimate"
"yes","1","R19","Resistor","240 Ω","power rating 250 mW","R_Axial_0207","metal film 240Ω 0.6 W, 1 %, 50 ppm/K (e.g. Vishay MBB0207)","Vishay / Yageo","any distributor (0207 1 %)","0.08","0.08","estimate"
"yes","1","R20","Resistor","2.05 kΩ","power rating 250 mW","R_Axial_0207","metal film 2.05kΩ 0.6 W, 1 %, 50 ppm/K (e.g. Vishay MBB0207)","Vishay / Yageo","any distributor (0207 1 %)","0.08","0.08","estimate"
"yes","18","R21 R22 R23 R25 R26 R27 R28 R45 R46 R47 R48 R49 R60 R61 R68 R69 R70 R71","Resistor","10 kΩ","power rating 250 mW","R_Axial_0207","metal film 10kΩ 0.6 W, 1 %, 50 ppm/K (e.g. Vishay MBB0207)","Vishay / Yageo","any distributor (0207 1 %)","0.08","1.44","estimate"
"yes","2","R24 R32","Resistor","1 kΩ","power rating 250 mW","R_Axial_0207","metal film 1kΩ 0.6 W, 1 %, 50 ppm/K (e.g. Vishay MBB0207)","Vishay / Yageo","any distributor (0207 1 %)","0.08","0.16","estimate"
"yes","1","R29","Resistor","68 kΩ","power rating 250 mW","R_Axial_0207","metal film 68kΩ 0.6 W, 1 %, 50 ppm/K (e.g. Vishay MBB0207)","Vishay / Yageo","any distributor (0207 1 %)","0.08","0.08","estimate"
"yes","1","R30","Resistor","680 kΩ","power rating 250 mW","R_Axial_0207","metal film 680kΩ 0.6 W, 1 %, 50 ppm/K (e.g. Vishay MBB0207)","Vishay / Yageo","any distributor (0207 1 %)","0.08","0.08","estimate"
"yes","5","R31 R55 R59 R64 R65","Resistor","100 kΩ","power rating 250 mW","R_Axial_0207","metal film 100kΩ 0.6 W, 1 %, 50 ppm/K (e.g. Vishay MBB0207)","Vishay / Yageo","any distributor (0207 1 %)","0.08","0.40","estimate"
"yes","8","R33 R34 R35 R36 R72 R73 R74 R75","Resistor","220 kΩ","power rating 250 mW","R_Axial_0207","metal film 220kΩ 0.6 W, 1 %, 50 ppm/K (e.g. Vishay MBB0207)","Vishay / Yageo","any distributor (0207 1 %)","0.08","0.64","estimate"
"yes","10","R37 R38 R39 R40 R53 R63 R76 R77 R78 R79","Resistor","22 kΩ","power rating 250 mW","R_Axial_0207","metal film 22kΩ 0.6 W, 1 %, 50 ppm/K (e.g. Vishay MBB0207)","Vishay / Yageo","any distributor (0207 1 %)","0.08","0.80","estimate"
"yes","5","R41 R42 R43 R44 R66","Resistor","10 MΩ","power rating 250 mW","R_Axial_0207","metal film 10MΩ 0.6 W, 1 %, 50 ppm/K (e.g. Vishay MBB0207)","Vishay / Yageo","any distributor (0207 1 %)","0.08","0.40","estimate"
"yes","4","R50 R52 R54 R67","Resistor","47 kΩ","power rating 250 mW","R_Axial_0207","metal film 47kΩ 0.6 W, 1 %, 50 ppm/K (e.g. Vishay MBB0207)","Vishay / Yageo","any distributor (0207 1 %)","0.08","0.32","estimate"
"yes","2","R51 R62","Resistor","9.09 kΩ","power rating 250 mW","R_Axial_0207","metal film 9.09kΩ 0.6 W, 1 %, 50 ppm/K (e.g. Vishay MBB0207)","Vishay / Yageo","any distributor (0207 1 %)","0.08","0.16","estimate"
"yes","1","R57","Resistor","4.7 kΩ","power rating 250 mW","R_Axial_0207","metal film 4.7kΩ 0.6 W, 1 %, 50 ppm/K (e.g. Vishay MBB0207)","Vishay / Yageo","any distributor (0207 1 %)","0.08","0.08","estimate"
"yes","1","SW1","Push-button","tactile 6 mm","current rating 1 A","SW_Tactile_6mm","tactile switch 6 × 6 mm, THT (e.g. Omron B3F-1000)","Omron","any distributor (tactile)","0.30","0.30","estimate"
"yes","1","T1","Transformer","0.075","primary inductance 20 H; coupling 0.995; primary resistance 200 Ω; secondary resistance 1.5 Ω","Transformer_Wires_P7.62","VB 4,5/1/15","Block","RS","11.00","11.00","estimate"
"yes","1","U3","Adjustable regulator","LM317HV","","TO-220_Vertical","LM317HVT/NOPB","Texas Instruments","Mouser 926-LM317HVT/NOPB; RS 197-7244","2.20","2.20","live"
"yes","1","U4","Shunt reference","TL431","","TO-92_Wide","TL431ACLP","Texas Instruments","any distributor (TO-92)","0.30","0.30","estimate"
"yes","2","U5 U6","555 timer","NE555","","DIP-8","NE555P","Texas Instruments","any distributor (DIP-8)","0.35","0.70","estimate"
"yes","4","U7 U11 U13 U15","NOR gate (4 in one package)","+12V","","DIP-14","CD4001BE","Texas Instruments","any distributor (DIP-14)","0.45","1.80","estimate"
"yes","3","U8 U9 U12","14-stage binary counter (CD4020)","+12V","","DIP-16","CD4020BE","Texas Instruments","any distributor (DIP-16)","0.55","1.65","estimate"
"yes","1","U10","Comparator (4 in one package)","LM339","","DIP-14","LM339N","Texas Instruments","any distributor (DIP-14)","0.45","0.45","estimate"
"yes","2","U14 U16","Comparator (2 in one package)","LM393","","DIP-8","LM393P","Texas Instruments","any distributor (DIP-8)","0.40","0.80","estimate"
"no","1","F2","Fuse","gG 2 A, 10×38, DIN-rail holder","cold resistance 50 mΩ","","gG 2 A 10×38 cartridge + DIN-rail fuse holder 1-pole 32 A (e.g. ABB E 91/32)","ABB / Mersen","electrical wholesale","6.00","6.00","estimate"
"no","2","K5 K7","Contactor","18 A, coil 230 V AC","","","LC1D18P7","Schneider Electric","RS; electrical wholesale","48.00","96.00","estimate"
"no","2","K6 K8","Relay","12 V interface","","","38.51.7.012.0050","Finder","RS; electrical wholesale","14.00","28.00","estimate"
"no","1","Q1","Circuit breaker 1-pole + N","M14 A","","","GV2ME16","Schneider Electric","RS; electrical wholesale","50.00","50.00","estimate"
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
